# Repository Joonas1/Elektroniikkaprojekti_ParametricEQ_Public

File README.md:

Ensimmäinen käynnistys: ESP32 käynnistyy oletuksena Access Point -tilassa (tukiasema).

    SSID: ESP32_Config

    Salasana: 12345678

Asetukset: Yhdistä laitteeseen ja mene selaimella osoitteeseen 192.168.4.1. Täällä voit asettaa kotiverkkosi Wi-Fi-tiedot sekä Firebase URL:n ja Secret-avaimen.

Paikallinen käyttö: Kun ESP32 on yhdistetty verkkoon, konfigurointisivu on edelleen saatavilla ESP32:n omassa lähiverkon IP-osoitteessa.

Firebase-yhteys: Luo oma Firebase-projekti (Realtime Database). Jotta etäohjaus toimii, syötä sama Firebase URL ja Secret sekä ESP32-laitteelle että etäohjaussivustolle.

Etäohjaus: Projektin web-kansiosta löytyvän sivuston voi hostata itse. Muista asettaa Firebase-tiedot sivuston asetuksiin.

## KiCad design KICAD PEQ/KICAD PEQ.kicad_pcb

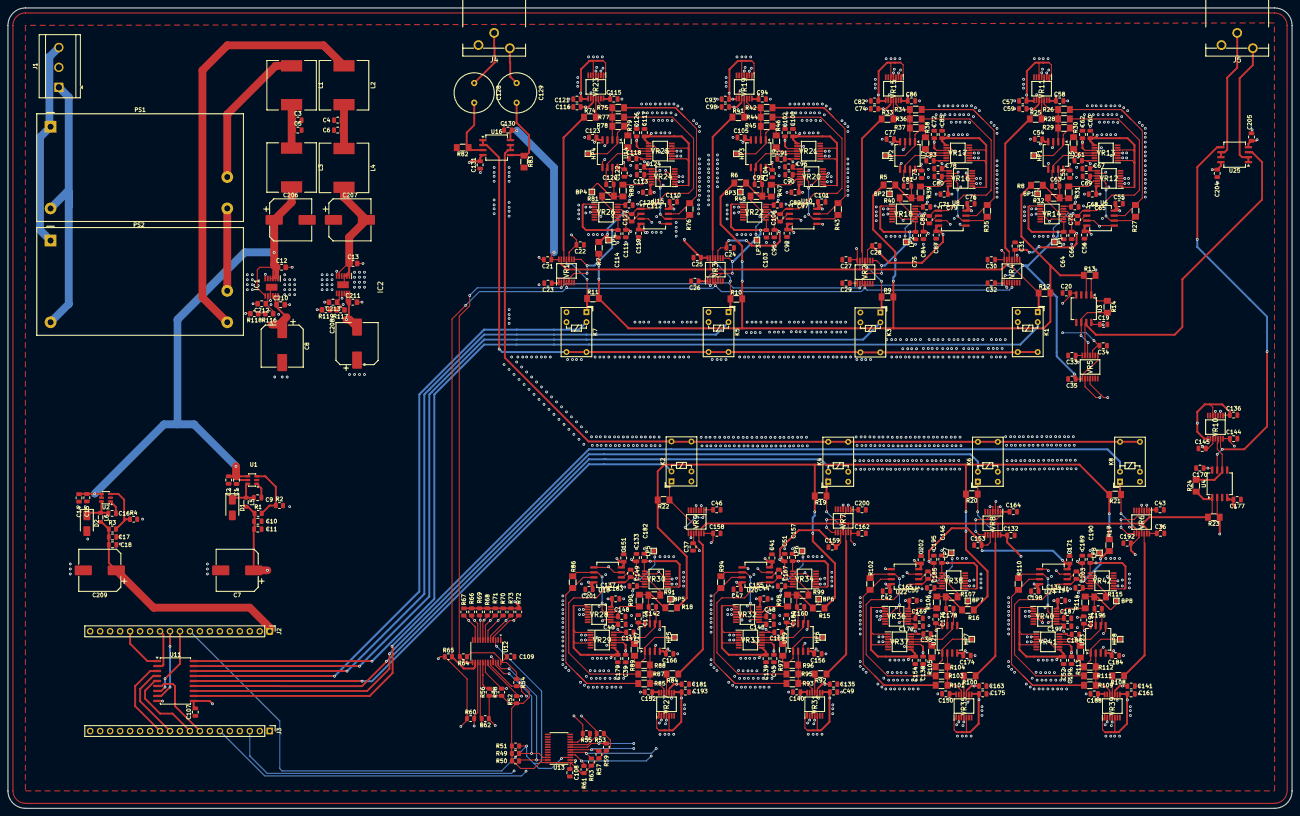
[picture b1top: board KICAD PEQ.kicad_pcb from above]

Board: 4 copper layers, 327.0 x 203.8 mm, 448 parts (0 on the bottom side), 192 nets.

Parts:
BP1, BP2, BP3, BP4, BP5, BP6, BP7, BP8: TestPoint; TestPoint_Pad_1.0x1.0mm
C1, C14: 10uF 25V; C_0805_2012Metric
C2, C5, C6, C10, C15, C17, C107, C108, C109: 100nF; C_0805_2012Metric
C3: 0.1uf; C_0805_2012Metric
C4: 1uF; C_0805_2012Metric
C7, C8, C206, C207, C208, C209: 470uF; CP_Elec_10x10.5
C9, C16: 10nF; C_0805_2012Metric
C11, C18: 22uF; C_0805_2012Metric
C12, C13, C210, C211, C212, C213: 10uF; C_0805_2012Metric_Pad1.18x1.45mm_HandSolder
C19, C20, C21, C22, C23, C24, C25, C26, C27, C28, C29, C30, C31, C32, C33, C34, C35, C36, C37, C38, C39, C40, C41, C42, C43, C44, C45, C46, C47, C48, C49, C50, C51, C52, C53, C54, C55, C56, C57, C58, C59, C60, C61, C62, C63, C64, C65, C66, C67, C68, C69, C70, C71, C72, C73, C74, C75, C76, C77, C78, C79, C80, C81, C82, C83, C84, C85, C86, C87, C88, C89, C90, C91, C92, C93, C94, C95, C96, C97, C98, C99, C100, C101, C102, C103, C104, C105, C106, C110, C111, C112, C113, C114, C115, C116, C117, C118, C119, C120, C121, C122, C123, C124, C125, C126, C127, C130, C131, C132, C133, C134, C135, C136, C137, C138, C139, C140, C141, C142, C143, C144, C145, C146, C147, C148, C149, C150, C151, C152, C153, C154, C155, C156, C157, C158, C159, C160, C161, C162, C163, C164, C165, C166, C167, C168, C169, C170, C171, C172, C173, C174, C175, C176, C177, C178, C179, C180, C181, C182, C183, C184, C185, C186, C187, C188, C189, C190, C191, C192, C193, C194, C195, C196, C197, C198, C199, C200, C201, C202, C203, C204, C205: C; C_0805_2012Metric
C128, C129: C; C_Radial_D10.0mm_H20.0mm_P5.00mm
D1, D2: SS34; D_SMA
HP1, HP2, HP3, HP4, HP5, HP6, HP7, HP8: TestPoint; TestPoint_Pad_1.0x1.0mm
IC1: LT3045EMSE#PBF; SOP65P490X110-13N
IC2: LT3094EMSE#PBF; SOP65P490X110-13N
J1: DB2EKM-7.62-3P-GN-S; TerminalBlock_CUI_TB007-508-03_1x03_P5.08mm_Horizontal
J2, J3: Conn_01x19_Socket; PinHeader_1x19_P2.54mm_Vertical
J4, J5: RCA_x2; CONN-TH_XDJK-0271-1650
K1, K2, K3, K4, K5, K6, K7, K8: Y14x-1C-xxDS; Relay_SPDT_HsinDa_Y14
L1, L2, L3, L4: 100uH; L_12x12mm_H8mm
L5, L6: 4.7uH; L_0805_2012Metric_Pad1.05x1.20mm_HandSolder
LP1, LP2, LP3, LP4, LP5, LP6, LP7, LP8: TestPoint; TestPoint_Pad_1.0x1.0mm
PS1, PS2: IRM-20-15; Converter_ACDC_MeanWell_IRM-20-xx_THT
R1: 64.9k; R_0805_2012Metric
R2, R49, R50, R51, R52, R53, R54, R55, R56, R57, R58, R59, R60, R61, R62, R63, R64, R65, R66, R67, R68, R69, R70, R71, R72, R73: 4.7k; R_0805_2012Metric
R3: 49.9k; R_0805_2012Metric
R4: 16.2k; R_0805_2012Metric
R5, R6, R7, R8, R9, R10, R11, R12, R13, R14, R15, R16, R17, R18, R19, R20, R21, R22, R23, R24, R25, R26, R27, R28, R29, R30, R31, R32, R33, R34, R35, R36, R37, R38, R39, R40, R41, R42, R43, R44, R45, R46, R47, R48, R74, R75, R76, R77, R78, R79, R80, R81, R82, R83, R84, R85, R86, R87, R88, R89, R90, R91, R92, R93, R94, R95, R96, R97, R98, R99, R100, R101, R102, R103, R104, R105, R106, R107, R108, R109, R110, R111, R112, R113, R114, R115: R; R_MiniMELF_MMA-0204
R116, R117: 130k; R_0805_2012Metric_Pad1.20x1.40mm_HandSolder
R118, R119: 15k; R_0805_2012Metric_Pad1.20x1.40mm_HandSolder
U1, U2: AP3211K; SOT-23-6
U3, U4, U5, U6, U7, U8, U9, U10, U14, U15, U16, U17, U18, U19, U20, U21, U22, U23, U24, U25: OPA1612AxD; SOIC-8_5.3x6.2mm_P1.27mm
U11: ULN2803A; SOIC-18W_7.5x11.6mm_P1.27mm
U12, U13: TCA9548APWR; TSSOP-24_4.4x7.8mm_P0.65mm
VR1, VR2, VR3, VR4, VR5, VR6, VR7, VR8, VR9, VR10, VR11, VR12, VR13, VR14, VR15, VR16, VR17, VR18, VR19, VR20, VR21, VR22, VR23, VR24, VR25, VR26, VR27, VR28, VR29, VR30, VR31, VR32, VR33, VR34, VR35, VR36, VR37, VR38, VR39, VR40, VR41, VR42: MCP41HV51-103E_ST; SOP65P640X120-14N

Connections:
/+3V3: C17.2, C18.2, C23.1, C26.1, C29.1, C32.1, C35.1, C40.1, C43.1, C46.1, C49.1, C52.1, C57.1, C60.1, C64.1, C67.1, C75.1, C78.1, C82.1, C85.1, C93.1, C96.1, C100.1, C103.1, C108.1, C109.1, C114.1, C117.1, C121.1, C124.1, C136.1, C139.1, C143.1, C146.1, C154.1, C157.1, C161.1, C164.1, C172.1, C175.1, C179.1, C182.1, C190.1, C193.1, C197.1, C200.1, C209.1, J2.1, L6.2, R3.1, R49.1, R50.1, R51.1, R52.1, R53.1, R54.1, R55.1, R56.1, R57.1, R58.1, R59.1, R60.1, R61.1, R62.1, R63.1, R64.1, R65.1, R66.1, R67.1, R68.1, R69.1, R70.1, R71.1, R72.1, R73.1, U12.24 (VCC), U13.1 (A0), U13.24 (VCC), VR1.1 (VL), VR1.3 (A1), VR1.5 (A0), VR1.8 (SHDN), VR2.1 (VL), VR2.3 (A1), VR2.8 (SHDN), VR3.1 (VL), VR3.5 (A0), VR3.8 (SHDN), VR4.1 (VL), VR4.8 (SHDN), VR5.1 (VL), VR5.8 (SHDN), VR6.1 (VL), VR6.3 (A1), VR6.5 (A0), VR6.8 (SHDN), VR7.1 (VL), VR7.3 (A1), VR7.8 (SHDN), VR8.1 (VL), VR8.5 (A0), VR8.8 (SHDN), VR9.1 (VL), VR9.8 (SHDN), VR10.1 (VL), VR10.5 (A0), VR10.8 (SHDN), VR11.1 (VL), VR11.3 (A1), VR11.5 (A0), VR11.8 (SHDN), VR12.1 (VL), VR12.8 (SHDN), VR13.1 (VL), VR13.5 (A0), VR13.8 (SHDN), VR14.1 (VL), VR14.3 (A1), VR14.8 (SHDN), VR15.1 (VL), VR15.3 (A1), VR15.5 (A0), VR15.8 (SHDN), VR16.1 (VL), VR16.8 (SHDN), VR17.1 (VL), VR17.5 (A0), VR17.8 (SHDN), VR18.1 (VL), VR18.3 (A1), VR18.8 (SHDN), VR19.1 (VL), VR19.3 (A1), VR19.5 (A0), VR19.8 (SHDN), VR20.1 (VL), VR20.8 (SHDN), VR21.1 (VL), VR21.5 (A0), VR21.8 (SHDN), VR22.1 (VL), VR22.3 (A1), VR22.8 (SHDN), VR23.1 (VL), VR23.3 (A1), VR23.5 (A0), VR23.8 (SHDN), VR24.1 (VL), VR24.8 (SHDN), VR25.1 (VL), VR25.5 (A0), VR25.8 (SHDN), VR26.1 (VL), VR26.3 (A1), VR26.8 (SHDN), VR27.1 (VL), VR27.3 (A1), VR27.5 (A0), VR27.8 (SHDN), VR28.1 (VL), VR28.8 (SHDN), VR29.1 (VL), VR29.5 (A0), VR29.8 (SHDN), VR30.1 (VL), VR30.3 (A1), VR30.8 (SHDN), VR31.1 (VL), VR31.3 (A1), VR31.5 (A0), VR31.8 (SHDN), VR32.1 (VL), VR32.8 (SHDN), VR33.1 (VL), VR33.5 (A0), VR33.8 (SHDN), VR34.1 (VL), VR34.3 (A1), VR34.8 (SHDN), VR35.1 (VL), VR35.3 (A1), VR35.5 (A0), VR35.8 (SHDN), VR36.1 (VL), VR36.8 (SHDN), VR37.1 (VL), VR37.5 (A0), VR37.8 (SHDN), VR38.1 (VL), VR38.3 (A1), VR38.8 (SHDN), VR39.1 (VL), VR39.3 (A1), VR39.5 (A0), VR39.8 (SHDN), VR40.1 (VL), VR40.8 (SHDN), VR41.1 (VL), VR41.5 (A0), VR41.8 (SHDN), VR42.1 (VL), VR42.3 (A1), VR42.8 (SHDN)
/+12V: C7.1, C10.2, C11.2, C107.2, L5.2, R1.1, U11.10 (COM)
/+15V: C8.1, C19.1, C21.1, C25.1, C27.1, C30.1, C33.1, C36.1, C38.1, C42.1, C44.1, C47.1, C50.1, C53.1, C55.1, C58.1, C61.1, C65.1, C68.1, C71.1, C73.1, C76.1, C79.1, C83.1, C86.1, C89.1, C91.1, C94.1, C97.1, C101.1, C104.1, C110.1, C112.1, C115.1, C118.1, C122.1, C125.1, C130.2, C132.1, C134.1, C137.1, C140.1, C144.1, C147.1, C150.1, C152.1, C155.1, C158.1, C162.1, C165.1, C168.1, C170.1, C173.1, C176.1, C180.1, C183.1, C186.1, C188.1, C191.1, C194.1, C198.1, C201.1, C204.2, C210.1, IC1.10 (OUTS), IC1.11 (OUT_1), IC1.12 (OUT_2), U3.8 (V+), U4.8 (V+), U5.8 (V+), U6.8 (V+), U7.8 (V+), U8.8 (V+), U9.8 (V+), U10.8 (V+), U14.8 (V+), U15.8 (V+), U16.8 (V+), U17.8 (V+), U18.8 (V+), U19.8 (V+), U20.8 (V+), U21.8 (V+), U22.8 (V+), U23.8 (V+), U24.8 (V+), U25.8 (V+), VR1.14 (V+), VR2.14 (V+), VR3.14 (V+), VR4.14 (V+), VR5.14 (V+), VR6.14 (V+), VR7.14 (V+), VR8.14 (V+), VR9.14 (V+), VR10.14 (V+), VR11.14 (V+), VR12.14 (V+), VR13.14 (V+), VR14.14 (V+), VR15.14 (V+), VR16.14 (V+), VR17.14 (V+), VR18.14 (V+), VR19.14 (V+), VR20.14 (V+), VR21.14 (V+), VR22.14 (V+), VR23.14 (V+), VR24.14 (V+), VR25.14 (V+), VR26.14 (V+), VR27.14 (V+), VR28.14 (V+), VR29.14 (V+), VR30.14 (V+), VR31.14 (V+), VR32.14 (V+), VR33.14 (V+), VR34.14 (V+), VR35.14 (V+), VR36.14 (V+), VR37.14 (V+), VR38.14 (V+), VR39.14 (V+), VR40.14 (V+), VR41.14 (V+), VR42.14 (V+)
/-15V: C20.2, C22.2, C24.2, C28.2, C31.2, C34.2, C37.2, C39.2, C41.2, C45.2, C48.2, C51.2, C54.2, C56.2, C59.2, C62.2, C66.2, C69.2, C72.2, C74.2, C77.2, C80.2, C84.2, C87.2, C90.2, C92.2, C95.2, C98.2, C102.2, C105.2, C111.2, C113.2, C116.2, C119.2, C123.2, C126.2, C131.2, C133.2, C135.2, C138.2, C141.2, C145.2, C148.2, C151.2, C153.2, C156.2, C159.2, C163.2, C166.2, C169.2, C171.2, C174.2, C177.2, C181.2, C184.2, C187.2, C189.2, C192.2, C195.2, C199.2, C202.2, C205.1, C208.2, C211.1, IC2.10 (OUTS), IC2.11 (OUT_1), IC2.12 (OUT_2), U3.4 (V-), U4.4 (V-), U5.4 (V-), U6.4 (V-), U7.4 (V-), U8.4 (V-), U9.4 (V-), U10.4 (V-), U14.4 (V-), U15.4 (V-), U16.4 (V-), U17.4 (V-), U18.4 (V-), U19.4 (V-), U20.4 (V-), U21.4 (V-), U22.4 (V-), U23.4 (V-), U24.4 (V-), U25.4 (V-), VR1.10 (V-), VR2.10 (V-), VR3.10 (V-), VR4.10 (V-), VR5.10 (V-), VR6.10 (V-), VR7.10 (V-), VR8.10 (V-), VR9.10 (V-), VR10.10 (V-), VR11.10 (V-), VR12.10 (V-), VR13.10 (V-), VR14.10 (V-), VR15.10 (V-), VR16.10 (V-), VR17.10 (V-), VR18.10 (V-), VR19.10 (V-), VR20.10 (V-), VR21.10 (V-), VR22.10 (V-), VR23.10 (V-), VR24.10 (V-), VR25.10 (V-), VR26.10 (V-), VR27.10 (V-), VR28.10 (V-), VR29.10 (V-), VR30.10 (V-), VR31.10 (V-), VR32.10 (V-), VR33.10 (V-), VR34.10 (V-), VR35.10 (V-), VR36.10 (V-), VR37.10 (V-), VR38.10 (V-), VR39.10 (V-), VR40.10 (V-), VR41.10 (V-), VR42.10 (V-)
/PEAK EQ L/IN: K2.5, K2.6, K4.5, K4.6, K6.5, K6.6, K8.5, K8.6, U16.6 (-), U16.7
/PEAK EQ L/OUT: U4.7, U25.5 (+), VR10.13 (P0A)
/PEAK EQ L/SCL_1: R58.2, U12.18 (SC6), VR27.2 (SCL), VR28.2 (SCL), VR29.2 (SCL), VR30.2 (SCL)
/PEAK EQ L/SCL_2: R54.2, U12.20 (SC7), VR31.2 (SCL), VR32.2 (SCL), VR33.2 (SCL), VR34.2 (SCL)
/PEAK EQ L/SCL_3: R63.2, U13.5 (SC0), VR35.2 (SCL), VR36.2 (SCL), VR37.2 (SCL), VR38.2 (SCL)
/PEAK EQ L/SCL_4: R59.2, U13.7 (SC1), VR39.2 (SCL), VR40.2 (SCL), VR41.2 (SCL), VR42.2 (SCL)
/PEAK EQ L/SCL_5: R55.2, U13.9 (SC2), VR6.2 (SCL), VR7.2 (SCL), VR8.2 (SCL), VR9.2 (SCL)
/PEAK EQ L/SCL_6: R62.2, U12.16 (SC5), VR5.2 (SCL), VR10.2 (SCL)
/PEAK EQ L/SDA_1: R56.2, U12.17 (SD6), VR27.4 (SDA), VR28.4 (SDA), VR29.4 (SDA), VR30.4 (SDA)
/PEAK EQ L/SDA_2: R52.2, U12.19 (SD7), VR31.4 (SDA), VR32.4 (SDA), VR33.4 (SDA), VR34.4 (SDA)
/PEAK EQ L/SDA_3: R61.2, U13.4 (SD0), VR35.4 (SDA), VR36.4 (SDA), VR37.4 (SDA), VR38.4 (SDA)
/PEAK EQ L/SDA_4: R57.2, U13.6 (SD1), VR39.4 (SDA), VR40.4 (SDA), VR41.4 (SDA), VR42.4 (SDA)
/PEAK EQ L/SDA_5: R53.2, U13.8 (SD2), VR6.4 (SDA), VR7.4 (SDA), VR8.4 (SDA), VR9.4 (SDA)
/PEAK EQ L/SDA_6: R60.2, U12.15 (SD5), VR5.4 (SDA), VR10.4 (SDA)
/PEAK EQ L/low shelf/BP: BP8.1, C196.2, R114.2, R115.1, U23.7
/PEAK EQ L/low shelf/HP: HP8.1, R112.2, R113.1, U23.1
/PEAK EQ L/low shelf/LP: C203.2, LP8.1, R17.1, R111.2, U24.1
/PEAK EQ L/low shelf/in: R108.1, VR6.12 (P0W)
/PEAK EQ L/lowshelf relay control: K8.3, U11.11 (O8)
/PEAK EQ L/peak 1/BP: BP5.1, C142.2, R18.1, R90.2, R91.1, U17.7
/PEAK EQ L/peak 1/HP: HP5.1, R88.2, R89.1, U17.1
/PEAK EQ L/peak 1/LP: C149.2, LP5.1, R87.2, U18.1
/PEAK EQ L/peak 1/in: R84.1, VR9.12 (P0W)
/PEAK EQ L/peak 2/BP: BP6.1, C160.2, R15.1, R98.2, R99.1, U19.7
/PEAK EQ L/peak 2/HP: HP6.1, R96.2, R97.1, U19.1
/PEAK EQ L/peak 2/LP: C167.2, LP6.1, R95.2, U20.1
/PEAK EQ L/peak 2/in: R92.1, VR7.12 (P0W)
/PEAK EQ L/peak 3/BP: BP7.1, C178.2, R16.1, R106.2, R107.1, U21.7
/PEAK EQ L/peak 3/HP: HP7.1, R104.2, R105.1, U21.1
/PEAK EQ L/peak 3/LP: C185.2, LP7.1, R103.2, U22.1
/PEAK EQ L/peak 3/in: R100.1, VR8.12 (P0W)
/PEAK EQ L/peak_1 relay control: K2.3, U11.14 (O5)
/PEAK EQ L/peak_2 relay control: K4.3, U11.13 (O6)
/PEAK EQ L/peak_3 relay control: K6.3, U11.12 (O7)
/PEAK EQ R/IN: K1.5, K1.6, K3.5, K3.6, K5.5, K5.6, K7.5, K7.6, U16.1, U16.2 (-)
/PEAK EQ R/OUT: U3.7, U25.3 (+), VR5.13 (P0A)
/PEAK EQ R/SCL_1: R73.2, U12.5 (SC0), VR11.2 (SCL), VR12.2 (SCL), VR13.2 (SCL), VR14.2 (SCL)
/PEAK EQ R/SCL_2: R71.2, U12.7 (SC1), VR15.2 (SCL), VR16.2 (SCL), VR17.2 (SCL), VR18.2 (SCL)
/PEAK EQ R/SCL_3: R69.2, U12.9 (SC2), VR19.2 (SCL), VR20.2 (SCL), VR21.2 (SCL), VR22.2 (SCL)
/PEAK EQ R/SCL_4: R67.2, U12.11 (SC3), VR23.2 (SCL), VR24.2 (SCL), VR25.2 (SCL), VR26.2 (SCL)
/PEAK EQ R/SCL_5: R64.2, U12.13 (SD4), VR1.2 (SCL), VR2.2 (SCL), VR3.2 (SCL), VR4.2 (SCL)
/PEAK EQ R/SDA_1: R72.2, U12.4 (SD0), VR11.4 (SDA), VR12.4 (SDA), VR13.4 (SDA), VR14.4 (SDA)
/PEAK EQ R/SDA_2: R70.2, U12.6 (SD1), VR15.4 (SDA), VR16.4 (SDA), VR17.4 (SDA), VR18.4 (SDA)
/PEAK EQ R/SDA_3: R68.2, U12.8 (SD2), VR19.4 (SDA), VR20.4 (SDA), VR21.4 (SDA), VR22.4 (SDA)
/PEAK EQ R/SDA_4: R66.2, U12.10 (SD3), VR23.4 (SDA), VR24.4 (SDA), VR25.4 (SDA), VR26.4 (SDA)
/PEAK EQ R/SDA_5: R65.2, U12.14 (SC4), VR1.4 (SDA), VR2.4 (SDA), VR3.4 (SDA), VR4.4 (SDA)
/PEAK EQ R/low shelf/BP: BP4.1, C120.2, R80.2, R81.1, U14.7
/PEAK EQ R/low shelf/HP: HP4.1, R78.2, R79.1, U14.1
/PEAK EQ R/low shelf/LP: C127.2, LP4.1, R7.1, R77.2, U15.1
/PEAK EQ R/low shelf/in: R74.1, VR1.12 (P0W)
/PEAK EQ R/lowshelf relay control: K7.3, U11.15 (O4)
/PEAK EQ R/peak 1/BP: BP1.1, C63.2, R8.1, R31.2, R32.1, U5.7
/PEAK EQ R/peak 1/HP: HP1.1, R29.2, R30.1, U5.1
/PEAK EQ R/peak 1/LP: C70.2, LP1.1, R28.2, U6.1
/PEAK EQ R/peak 1/in: R25.1, VR4.12 (P0W)
/PEAK EQ R/peak 2/BP: BP2.1, C81.2, R5.1, R39.2, R40.1, U7.7
/PEAK EQ R/peak 2/HP: HP2.1, R37.2, R38.1, U7.1
/PEAK EQ R/peak 2/LP: C88.2, LP2.1, R36.2, U8.1
/PEAK EQ R/peak 2/in: R33.1, VR2.12 (P0W)
/PEAK EQ R/peak 3/BP: BP3.1, C99.2, R6.1, R47.2, R48.1, U9.7
/PEAK EQ R/peak 3/HP: HP3.1, R45.2, R46.1, U9.1
/PEAK EQ R/peak 3/LP: C106.2, LP3.1, R44.2, U10.1
/PEAK EQ R/peak 3/in: R41.1, VR3.12 (P0W)
/PEAK EQ R/peak_1 relay control: K1.3, U11.18 (O1)
/PEAK EQ R/peak_2 relay control: K3.3, U11.17 (O2)
/PEAK EQ R/peak_3 relay control: K5.3, U11.16 (O3)
/esp32/IO13: J2.15, U11.1 (I1)
/esp32/IO14: J2.12, U11.2 (I2)
/esp32/IO16: J3.12, U11.3 (I3)
/esp32/IO17: J3.11, U11.4 (I4)
/esp32/IO18: J3.9, U11.5 (I5)
/esp32/IO19: J3.8, U11.6 (I6)
/esp32/IO21: J3.6, R50.2, U12.23 (SDA), U13.23 (SDA)
/esp32/IO22: J3.3, R49.2, U12.22 (SCL), U13.22 (SCL)
/esp32/IO25: J2.9, R51.2, U12.3 (~RESET), U13.3 (~RESET)
/esp32/IO26: J2.10, U11.7 (I7)
/esp32/IO27: J2.11, U11.8 (I8)
GND: C1.1, C2.1, C3.2, C4.2, C5.2, C6.2, C7.2, C8.2, C10.1, C11.1, C12.2, C13.2, C14.1, C15.1, C17.1, C18.1, C19.2, C20.1, C21.2, C22.1, C23.2, C24.1, C25.2, C26.2, C27.2, C28.1, C29.2, C30.2, C31.1, C32.2, C33.2, C34.1, C35.2, C36.2, C37.1, C38.2, C39.1, C40.2, C41.1, C42.2, C43.2, C44.2, C45.1, C46.2, C47.2, C48.1, C49.2, C50.2, C51.1, C52.2, C53.2, C54.1, C55.2, C56.1, C57.2, C58.2, C59.1, C60.2, C61.2, C62.1, C64.2, C65.2, C66.1, C67.2, C68.2, C69.1, C71.2, C72.1, C73.2, C74.1, C75.2, C76.2, C77.1, C78.2, C79.2, C80.1, C82.2, C83.2, C84.1, C85.2, C86.2, C87.1, C89.2, C90.1, C91.2, C92.1, C93.2, C94.2, C95.1, C96.2, C97.2, C98.1, C100.2, C101.2, C102.1, C103.2, C104.2, C105.1, C107.1, C108.2, C109.2, C110.2, C111.1, C112.2, C113.1, C114.2, C115.2, C116.1, C117.2, C118.2, C119.1, C121.2, C122.2, C123.1, C124.2, C125.2, C126.1, C130.1, C131.1, C132.2, C133.1, C134.2, C135.1, C136.2, C137.2, C138.1, C139.2, C140.2, C141.1, C143.2, C144.2, C145.1, C146.2, C147.2, C148.1, C150.2, C151.1, C152.2, C153.1, C154.2, C155.2, C156.1, C157.2, C158.2, C159.1, C161.2, C162.2, C163.1, C164.2, C165.2, C166.1, C168.2, C169.1, C170.2, C171.1, C172.2, C173.2, C174.1, C175.2, C176.2, C177.1, C179.2, C180.2, C181.1, C182.2, C183.2, C184.1, C186.2, C187.1, C188.2, C189.1, C190.2, C191.2, C192.1, C193.2, C194.2, C195.1, C197.2, C198.2, C199.1, C200.2, C201.2, C202.1, C204.1, C205.2, C206.2, C207.1, C208.1, C209.2, C210.2, C211.2, C212.2, C213.2, D1.2 (A), D2.2 (A), IC1.6 (ILIM), IC1.9 (GND_1), IC1.13 (GND_2), IC2.6 (ILIM), IC2.9 (GND), J1.2, J3.1, J4.3 (EXT), J5.3 (EXT), K1.4, K2.4, K3.4, K4.4, K5.4, K6.4, K7.4, K8.4, PS1.3 (-Vo), PS2.4 (+Vo), R2.2, R4.2, R82.2, R83.2, R118.2, R119.2, U1.2 (GND), U2.2 (GND), U3.3 (+), U3.5 (+), U4.3 (+), U4.5 (+), U5.3 (+), U5.5 (+), U6.3 (+), U6.5 (+), U7.3 (+), U7.5 (+), U8.3 (+), U8.5 (+), U9.3 (+), U9.5 (+), U10.3 (+), U10.5 (+), U11.9 (GND), U12.1 (A0), U12.2 (A1), U12.12 (GND), U12.21 (A2), U13.2 (A1), U13.12 (GND), U13.21 (A2), U14.3 (+), U14.5 (+), U15.3 (+), U15.5 (+), U17.3 (+), U17.5 (+), U18.3 (+), U18.5 (+), U19.3 (+), U19.5 (+), U20.3 (+), U20.5 (+), U21.3 (+), U21.5 (+), U22.3 (+), U22.5 (+), U23.3 (+), U23.5 (+), U24.3 (+), U24.5 (+), VR1.9 (DGND), VR2.5 (A0), VR2.9 (DGND), VR3.3 (A1), VR3.9 (DGND), VR4.3 (A1), VR4.5 (A0), VR4.9 (DGND), VR5.3 (A1), VR5.5 (A0), VR5.9 (DGND), VR6.9 (DGND), VR7.5 (A0), VR7.9 (DGND), VR8.3 (A1), VR8.9 (DGND), VR9.3 (A1), VR9.5 (A0), VR9.9 (DGND), VR10.3 (A1), VR10.9 (DGND), VR11.9 (DGND), VR12.3 (A1), VR12.5 (A0), VR12.9 (DGND), VR13.3 (A1), VR13.9 (DGND), VR14.5 (A0), VR14.9 (DGND), VR15.9 (DGND), VR16.3 (A1), VR16.5 (A0), VR16.9 (DGND), VR17.3 (A1), VR17.9 (DGND), VR18.5 (A0), VR18.9 (DGND), VR19.9 (DGND), VR20.3 (A1), VR20.5 (A0), VR20.9 (DGND), VR21.3 (A1), VR21.9 (DGND), VR22.5 (A0), VR22.9 (DGND), VR23.9 (DGND), VR24.3 (A1), VR24.5 (A0), VR24.9 (DGND), VR25.3 (A1), VR25.9 (DGND), VR26.5 (A0), VR26.9 (DGND), VR27.9 (DGND), VR28.3 (A1), VR28.5 (A0), VR28.9 (DGND), VR29.3 (A1), VR29.9 (DGND), VR30.5 (A0), VR30.9 (DGND), VR31.9 (DGND), VR32.3 (A1), VR32.5 (A0), VR32.9 (DGND), VR33.3 (A1), VR33.9 (DGND), VR34.5 (A0), VR34.9 (DGND), VR35.9 (DGND), VR36.3 (A1), VR36.5 (A0), VR36.9 (DGND), VR37.3 (A1), VR37.9 (DGND), VR38.5 (A0), VR38.9 (DGND), VR39.9 (DGND), VR40.3 (A1), VR40.5 (A0), VR40.9 (DGND), VR41.3 (A1), VR41.9 (DGND), VR42.5 (A0), VR42.9 (DGND)
unnamed: C3.1, C5.1, L1.2, L3.1
unnamed: C4.1, C6.1, L2.2, L4.1
unnamed: C9.1, D1.1 (K), L5.1, U1.6 (SW)
unnamed: C16.1, D2.1 (K), L6.1, U2.6 (SW)
unnamed: C1.2, C2.2, C12.1, C14.2, C15.2, C206.1, IC1.1 (IN_1), IC1.2 (IN_2), IC1.3 (IN_3), IC1.4 (EN/UV), IC1.7 (PGFB), L3.2, U1.4 (EN), U1.5 (IN), U2.4 (EN), U2.5 (IN)
unnamed: C212.1, IC1.8 (SET), R116.1
unnamed: C13.1, C207.2, IC2.1 (IN_1), IC2.2 (IN_2), IC2.3 (EN/UV), IC2.5 (PGFB), IC2.13 (IN_3), L4.2
unnamed: C213.1, IC2.8 (SET), R117.1
unnamed: J1.1, PS1.2 (AC/N), PS2.2 (AC/N)
unnamed: J1.3, PS1.1 (AC/L), PS2.1 (AC/L)
unnamed: C129.1, J4.1 (IN1)
unnamed: C128.1, J4.2 (IN2)
unnamed: J5.1 (IN1), U25.1, U25.2 (-)
unnamed: J5.2 (IN2), U25.6 (-), U25.7
unnamed: L1.1, PS1.4 (+Vo)
unnamed: L2.1, PS2.3 (-Vo)
unnamed: R26.1, R27.1, U6.7
unnamed: R34.1, R35.1, U8.7
unnamed: R42.1, R43.1, U10.7
unnamed: R75.1, R76.1, U15.7
unnamed: R85.1, R86.1, U18.7
unnamed: R93.1, R94.1, U20.7
unnamed: R101.1, R102.1, U22.7
unnamed: R109.1, R110.1, U24.7
unnamed: R116.2, R118.1
unnamed: R117.2, R119.1
unnamed: C9.2, U1.1 (BS)
unnamed: R1.2, R2.1, U1.3 (FB)
unnamed: C16.2, U2.1 (BS)
unnamed: R3.2, R4.1, U2.3 (FB)
unnamed: R5.2, R6.2, R7.2, R8.2, R9.2, R10.2, R11.2, R12.2, R13.1, U3.2 (-)
unnamed: R14.2, U3.6 (-), VR5.12 (P0W)
unnamed: R15.2, R16.2, R17.2, R18.2, R19.2, R20.2, R21.2, R22.2, R23.1, U4.2 (-)
unnamed: R24.2, U4.6 (-), VR10.12 (P0W)
unnamed: R26.2, R28.1, R29.1, U5.2 (-), VR11.12 (P0W)
unnamed: C63.1, U5.6 (-), VR13.12 (P0W)
unnamed: C70.1, U6.2 (-), VR14.12 (P0W)
unnamed: R27.2, U6.6 (-), VR12.11 (P0B)
unnamed: R34.2, R36.1, R37.1, U7.2 (-), VR15.12 (P0W)
unnamed: C81.1, U7.6 (-), VR17.12 (P0W)
unnamed: C88.1, U8.2 (-), VR18.12 (P0W)
unnamed: R35.2, U8.6 (-), VR16.11 (P0B)
unnamed: R42.2, R44.1, R45.1, U9.2 (-), VR19.12 (P0W)
unnamed: C99.1, U9.6 (-), VR21.12 (P0W)
unnamed: C106.1, U10.2 (-), VR22.12 (P0W)
unnamed: R43.2, U10.6 (-), VR20.11 (P0B)
unnamed: R75.2, R77.1, R78.1, U14.2 (-), VR23.12 (P0W)
unnamed: C120.1, U14.6 (-), VR25.12 (P0W)
unnamed: C127.1, U15.2 (-), VR26.12 (P0W)
unnamed: R76.2, U15.6 (-), VR24.11 (P0B)
unnamed: C128.2, R82.1, U16.3 (+)
unnamed: C129.2, R83.1, U16.5 (+)
unnamed: R85.2, R87.1, R88.1, U17.2 (-), VR27.12 (P0W)
unnamed: C142.1, U17.6 (-), VR29.12 (P0W)
unnamed: C149.1, U18.2 (-), VR30.12 (P0W)
unnamed: R86.2, U18.6 (-), VR28.11 (P0B)
unnamed: R93.2, R95.1, R96.1, U19.2 (-), VR31.12 (P0W)
unnamed: C160.1, U19.6 (-), VR33.12 (P0W)
unnamed: C167.1, U20.2 (-), VR34.12 (P0W)
unnamed: R94.2, U20.6 (-), VR32.11 (P0B)
unnamed: R101.2, R103.1, R104.1, U21.2 (-), VR35.12 (P0W)
unnamed: C178.1, U21.6 (-), VR37.12 (P0W)
unnamed: C185.1, U22.2 (-), VR38.12 (P0W)
unnamed: R102.2, U22.6 (-), VR36.11 (P0B)
unnamed: R109.2, R111.1, R112.1, U23.2 (-), VR39.12 (P0W)
unnamed: C196.1, U23.6 (-), VR41.12 (P0W)
unnamed: C203.1, U24.2 (-), VR42.12 (P0W)
unnamed: R110.2, U24.6 (-), VR40.11 (P0B)
unnamed: R13.2, R14.1, U3.1, VR1.13 (P0A), VR2.13 (P0A), VR3.13 (P0A), VR4.13 (P0A)
unnamed: K7.1, R11.1, VR1.11 (P0B)
unnamed: K3.1, R9.1, VR2.11 (P0B)
unnamed: K5.1, R10.1, VR3.11 (P0B)
unnamed: K1.1, R12.1, VR4.11 (P0B)
unnamed: R23.2, R24.1, U4.1, VR6.13 (P0A), VR7.13 (P0A), VR8.13 (P0A), VR9.13 (P0A)
unnamed: K8.1, R21.1, VR6.11 (P0B)
unnamed: K4.1, R19.1, VR7.11 (P0B)
unnamed: K6.1, R20.1, VR8.11 (P0B)
unnamed: K2.1, R22.1, VR9.11 (P0B)
unnamed: R25.2, VR11.11 (P0B)
unnamed: R31.1, VR12.12 (P0W)
unnamed: R30.2, VR13.11 (P0B)
unnamed: R32.2, VR14.11 (P0B)
unnamed: R33.2, VR15.11 (P0B)
unnamed: R39.1, VR16.12 (P0W)
unnamed: R38.2, VR17.11 (P0B)
unnamed: R40.2, VR18.11 (P0B)
unnamed: R41.2, VR19.11 (P0B)
unnamed: R47.1, VR20.12 (P0W)
unnamed: R46.2, VR21.11 (P0B)
unnamed: R48.2, VR22.11 (P0B)
unnamed: R74.2, VR23.11 (P0B)
unnamed: R80.1, VR24.12 (P0W)
unnamed: R79.2, VR25.11 (P0B)
unnamed: R81.2, VR26.11 (P0B)
unnamed: R84.2, VR27.11 (P0B)
unnamed: R90.1, VR28.12 (P0W)
unnamed: R89.2, VR29.11 (P0B)
unnamed: R91.2, VR30.11 (P0B)
unnamed: R92.2, VR31.11 (P0B)
unnamed: R98.1, VR32.12 (P0W)
unnamed: R97.2, VR33.11 (P0B)
unnamed: R99.2, VR34.11 (P0B)
unnamed: R100.2, VR35.11 (P0B)
unnamed: R106.1, VR36.12 (P0W)
unnamed: R105.2, VR37.11 (P0B)
unnamed: R107.2, VR38.11 (P0B)
unnamed: R108.2, VR39.11 (P0B)
unnamed: R114.1, VR40.12 (P0W)
unnamed: R113.2, VR41.11 (P0B)
unnamed: R115.2, VR42.11 (P0B)

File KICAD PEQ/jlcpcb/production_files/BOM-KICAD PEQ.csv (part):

Comment,Designator,Footprint,LCSC,Quantity
C,C160,C_0805_2012Metric,,1
MCP41HV51-103E_ST,VR35,SOP65P640X120-14N,,1
C,C62,C_0805_2012Metric,,1
470uF,C208,CP_Elec_10x10.5,,1
C,C87,C_0805_2012Metric,,1
C,C31,C_0805_2012Metric,,1
R,R16,R_MiniMELF_MMA-0204,,1
C,C171,C_0805_2012Metric,,1
C,C200,C_0805_2012Metric,,1
C,C73,C_0805_2012Metric,,1
470uF,C209,CP_Elec_10x10.5,,1
C,C184,C_0805_2012Metric,,1
C,C80,C_0805_2012Metric,,1
4.7k,R72,R_0805_2012Metric,,1
C,C161,C_0805_2012Metric,,1
C,C91,C_0805_2012Metric,,1
4.7k,R57,R_0805_2012Metric,,1
100uH,L1,L_12x12mm_H8mm,,1
C,C101,C_0805_2012Metric,,1
4.7k,R68,R_0805_2012Metric,,1
OPA1612AxD,U5,SOIC-8_5.3x6.2mm_P1.27mm,,1
R,R80,R_MiniMELF_MMA-0204,,1
C,C186,C_0805_2012Metric,,1
C,C190,C_0805_2012Metric,,1
MCP41HV51-103E_ST,VR4,SOP65P640X120-14N,,1
C,C173,C_0805_2012Metric,,1
RCA_x2,J4,CONN-TH_XDJK-0271-1650,,1
4.7uH,L5,L_0805_2012Metric_Pad1.05x1.20mm_HandSolder,,1
OPA1612AxD,U7,SOIC-8_5.3x6.2mm_P1.27mm,,1
4.7k,R56,R_0805_2012Metric,,1
C,C153,C_0805_2012Metric,,1
C,C72,C_0805_2012Metric,,1
4.7k,R53,R_0805_2012Metric,,1
OPA1612AxD,U15,SOIC-8_5.3x6.2mm_P1.27mm,,1
MCP41HV51-103E_ST,VR28,SOP65P640X120-14N,,1
AP3211K,U2,SOT-23-6,,1
R,R84,R_MiniMELF_MMA-0204,,1
TestPoint,BP5,TestPoint_Pad_1.0x1.0mm,,1
C,C178,C_0805_2012Metric,,1
R,R110,R_MiniMELF_MMA-0204,,1
R,R42,R_MiniMELF_MMA-0204,,1
10nF,C9,C_0805_2012Metric,,1
MCP41HV51-103E_ST,VR15,SOP65P640X120-14N,,1
C,C84,C_0805_2012Metric,,1
R,R100,R_MiniMELF_MMA-0204,,1
4.7k,R69,R_0805_2012Metric,,1
C,C96,C_0805_2012Metric,,1
470uF,C7,CP_Elec_10x10.5,,1
100nF,C6,C_0805_2012Metric,,1
R,R104,R_MiniMELF_MMA-0204,,1
C,C158,C_0805_2012Metric,,1
TestPoint,BP6,TestPoint_Pad_1.0x1.0mm,,1
MCP41HV51-103E_ST,VR2,SOP65P640X120-14N,,1
R,R13,R_MiniMELF_MMA-0204,,1
C,C23,C_0805_2012Metric,,1
R,R106,R_MiniMELF_MMA-0204,,1
OPA1612AxD,U16,SOIC-8_5.3x6.2mm_P1.27mm,,1
C,C21,C_0805_2012Metric,,1
R,R17,R_MiniMELF_MMA-0204,,1
C,C67,C_0805_2012Metric,,1
Y14x-1C-xxDS,K5,Relay_SPDT_HsinDa_Y14,,1
MCP41HV51-103E_ST,VR40,SOP65P640X120-14N,,1
TestPoint,HP8,TestPoint_Pad_1.0x1.0mm,,1
10nF,C16,C_0805_2012Metric,,1
C,C71,C_0805_2012Metric,,1
C,C182,C_0805_2012Metric,,1
C,C183,C_0805_2012Metric,,1
C,C143,C_0805_2012Metric,,1
TestPoint,HP3,TestPoint_Pad_1.0x1.0mm,,1
C,C38,C_0805_2012Metric,,1
C,C135,C_0805_2012Metric,,1
C,C189,C_0805_2012Metric,,1
C,C47,C_0805_2012Metric,,1
C,C138,C_0805_2012Metric,,1
C,C132,C_0805_2012Metric,,1
C,C45,C_0805_2012Metric,,1
4.7k,R55,R_0805_2012Metric,,1
R,R78,R_MiniMELF_MMA-0204,,1
100uH,L4,L_12x12mm_H8mm,,1
OPA1612AxD,U3,SOIC-8_5.3x6.2mm_P1.27mm,,1
C,C76,C_0805_2012Metric,,1
C,C180,C_0805_2012Metric,,1
C,C111,C_0805_2012Metric,,1
470uF,C207,CP_Elec_10x10.5,,1
C,C127,C_0805_2012Metric,,1
C,C110,C_0805_2012Metric,,1
MCP41HV51-103E_ST,VR20,SOP65P640X120-14N,,1
C,C89,C_0805_2012Metric,,1
R,R32,R_MiniMELF_MMA-0204,,1
R,R105,R_MiniMELF_MMA-0204,,1
C,C172,C_0805_2012Metric,,1
R,R29,R_MiniMELF_MMA-0204,,1
C,C88,C_0805_2012Metric,,1
R,R98,R_MiniMELF_MMA-0204,,1
C,C63,C_0805_2012Metric,,1
R,R7,R_MiniMELF_MMA-0204,,1
C,C30,C_0805_2012Metric,,1
R,R20,R_MiniMELF_MMA-0204,,1
MCP41HV51-103E_ST,VR6,SOP65P640X120-14N,,1
C,C53,C_0805_2012Metric,,1
4.7k,R49,R_0805_2012Metric,,1
C,C167,C_0805_2012Metric,,1
MCP41HV51-103E_ST,VR23,SOP65P640X120-14N,,1
TestPoint,LP8,TestPoint_Pad_1.0x1.0mm,,1
4.7k,R70,R_0805_2012Metric,,1
ULN2803A,U11,SOIC-18W_7.5x11.6mm_P1.27mm,,1
C,C116,C_0805_2012Metric,,1
470uF,C206,CP_Elec_10x10.5,,1
C,C78,C_0805_2012Metric,,1
R,R81,R_MiniMELF_MMA-0204,,1
Y14x-1C-xxDS,K4,Relay_SPDT_HsinDa_Y14,,1
R,R28,R_MiniMELF_MMA-0204,,1
C,C68,C_0805_2012Metric,,1
4.7k,R58,R_0805_2012Metric,,1
100nF,C107,C_0805_2012Metric,,1
100nF,C15,C_0805_2012Metric,,1
64.9k,R1,R_0805_2012Metric,,1
C,C198,C_0805_2012Metric,,1
R,R26,R_MiniMELF_MMA-0204,,1
R,R40,R_MiniMELF_MMA-0204,,1
AP3211K,U1,SOT-23-6,,1
C,C77,C_0805_2012Metric,,1
C,C102,C_0805_2012Metric,,1
C,C162,C_0805_2012Metric,,1
C,C25,C_0805_2012Metric,,1
4.7k,R60,R_0805_2012Metric,,1
MCP41HV51-103E_ST,VR24,SOP65P640X120-14N,,1
MCP41HV51-103E_ST,VR41,SOP65P640X120-14N,,1
C,C123,C_0805_2012Metric,,1
C,C74,C_0805_2012Metric,,1
IRM-20-15,PS2,Converter_ACDC_MeanWell_IRM-20-xx_THT,,1
MCP41HV51-103E_ST,VR19,SOP65P640X120-14N,,1
R,R19,R_MiniMELF_MMA-0204,,1
C,C168,C_0805_2012Metric,,1
TestPoint,BP7,TestPoint_Pad_1.0x1.0mm,,1
C,C24,C_0805_2012Metric,,1
C,C118,C_0805_2012Metric,,1
R,R103,R_MiniMELF_MMA-0204,,1
C,C35,C_0805_2012Metric,,1
C,C59,C_0805_2012Metric,,1
C,C131,C_0805_2012Metric,,1
R,R6,R_MiniMELF_MMA-0204,,1
TestPoint,LP5,TestPoint_Pad_1.0x1.0mm,,1
SS34,D2,D_SMA,,1
R,R108,R_MiniMELF_MMA-0204,,1
C,C49,C_0805_2012Metric,,1
R,R39,R_MiniMELF_MMA-0204,,1
C,C100,C_0805_2012Metric,,1
100uH,L2,L_12x12mm_H8mm,,1
OPA1612AxD,U23,SOIC-8_5.3x6.2mm_P1.27mm,,1
C,C170,C_0805_2012Metric,,1
Conn_01x19_Socket,J3,PinHeader_1x19_P2.54mm_Vertical,,1
C,C51,C_0805_2012Metric,,1
C,C90,C_0805_2012Metric,,1
R,R47,R_MiniMELF_MMA-0204,,1
C,C157,C_0805_2012Metric,,1
C,C150,C_0805_2012Metric,,1
MCP41HV51-103E_ST,VR34,SOP65P640X120-14N,,1
R,R99,R_MiniMELF_MMA-0204,,1
Y14x-1C-xxDS,K6,Relay_SPDT_HsinDa_Y14,,1
MCP41HV51-103E_ST,VR36,SOP65P640X120-14N,,1
C,C69,C_0805_2012Metric,,1
1uF,C4,C_0805_2012Metric,,1
C,C79,C_0805_2012Metric,,1
C,C42,C_0805_2012Metric,,1
Y14x-1C-xxDS,K2,Relay_SPDT_HsinDa_Y14,,1
MCP41HV51-103E_ST,VR22,SOP65P640X120-14N,,1
49.9k,R3,R_0805_2012Metric,,1
TestPoint,BP2,TestPoint_Pad_1.0x1.0mm,,1
MCP41HV51-103E_ST,VR25,SOP65P640X120-14N,,1
IRM-20-15,PS1,Converter_ACDC_MeanWell_IRM-20-xx_THT,,1
C,C187,C_0805_2012Metric,,1
R,R93,R_MiniMELF_MMA-0204,,1
TestPoint,LP1,TestPoint_Pad_1.0x1.0mm,,1
100nF,C109,C_0805_2012Metric,,1
R,R37,R_MiniMELF_MMA-0204,,1
R,R8,R_MiniMELF_MMA-0204,,1
MCP41HV51-103E_ST,VR42,SOP65P640X120-14N,,1
0.1uf,C3,C_0805_2012Metric,,1
C,C164,C_0805_2012Metric,,1
MCP41HV51-103E_ST,VR39,SOP65P640X120-14N,,1
100nF,C10,C_0805_2012Metric,,1
C,C193,C_0805_2012Metric,,1
C,C130,C_0805_2012Metric,,1
OPA1612AxD,U19,SOIC-8_5.3x6.2mm_P1.27mm,,1
10uF 25V,C1,C_0805_2012Metric,,1
MCP41HV51-103E_ST,VR3,SOP65P640X120-14N,,1
Y14x-1C-xxDS,K7,Relay_SPDT_HsinDa_Y14,,1
C,C148,C_0805_2012Metric,,1
R,R75,R_MiniMELF_MMA-0204,,1
R,R33,R_MiniMELF_MMA-0204,,1
C,C191,C_0805_2012Metric,,1
R,R94,R_MiniMELF_MMA-0204,,1
MCP41HV51-103E_ST,VR14,SOP65P640X120-14N,,1
RCA_x2,J5,CONN-TH_XDJK-0271-1650,,1
22uF,C11,C_0805_2012Metric,,1
R,R79,R_MiniMELF_MMA-0204,,1
C,C113,C_0805_2012Metric,,1
SS34,D1,D_SMA,,1
C,C133,C_0805_2012Metric,,1
C,C52,C_0805_2012Metric,,1
C,C122,C_0805_2012Metric,,1
R,R86,R_MiniMELF_MMA-0204,,1
C,C159,C_0805_2012Metric,,1
C,C66,C_0805_2012Metric,,1
MCP41HV51-103E_ST,VR38,SOP65P640X120-14N,,1
C,C106,C_0805_2012Metric,,1
100nF,C5,C_0805_2012Metric,,1
C,C205,C_0805_2012Metric,,1
C,C28,C_0805_2012Metric,,1
4.7k,R50,R_0805_2012Metric,,1
R,R21,R_MiniMELF_MMA-0204,,1
R,R83,R_MiniMELF_MMA-0204,,1
MCP41HV51-103E_ST,VR26,SOP65P640X120-14N,,1
470uF,C8,CP_Elec_10x10.5,,1
C,C104,C_0805_2012Metric,,1
C,C60,C_0805_2012Metric,,1
C,C75,C_0805_2012Metric,,1
R,R23,R_MiniMELF_MMA-0204,,1
10uF 25V,C14,C_0805_2012Metric,,1
C,C145,C_0805_2012Metric,,1
R,R82,R_MiniMELF_MMA-0204,,1
TCA9548APWR,U13,TSSOP-24_4.4x7.8mm_P0.65mm,,1
C,C103,C_0805_2012Metric,,1
C,C26,C_0805_2012Metric,,1
C,C204,C_0805_2012Metric,,1
4.7k,R63,R_0805_2012Metric,,1
R,R89,R_MiniMELF_MMA-0204,,1
R,R115,R_MiniMELF_MMA-0204,,1
C,C195,C_0805_2012Metric,,1
R,R77,R_MiniMELF_MMA-0204,,1
C,C34,C_0805_2012Metric,,1
C,C155,C_0805_2012Metric,,1
TestPoint,BP1,TestPoint_Pad_1.0x1.0mm,,1
C,C119,C_0805_2012Metric,,1
C,C156,C_0805_2012Metric,,1
OPA1612AxD,U10,SOIC-8_5.3x6.2mm_P1.27mm,,1
4.7k,R54,R_0805_2012Metric,,1
C,C81,C_0805_2012Metric,,1
C,C142,C_0805_2012Metric,,1
R,R113,R_MiniMELF_MMA-0204,,1
C,C64,C_0805_2012Metric,,1
C,C146,C_0805_2012Metric,,1
100nF,C17,C_0805_2012Metric,,1
C,C83,C_0805_2012Metric,,1
C,C176,C_0805_2012Metric,,1
MCP41HV51-103E_ST,VR18,SOP65P640X120-14N,,1
C,C27,C_0805_2012Metric,,1
TestPoint,HP6,TestPoint_Pad_1.0x1.0mm,,1
R,R74,R_MiniMELF_MMA-0204,,1
Conn_01x19_Socket,J2,PinHeader_1x19_P2.54mm_Vertical,,1
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
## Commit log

2025-12-28 Initial public release
2026-01-08 Add initial README content for ESP32 project
2026-01-08 Fix formatting issue in README.md
